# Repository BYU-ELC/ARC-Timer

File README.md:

# ARC-Timer
Autonomous Robotics Competition (BYU) Match Timer

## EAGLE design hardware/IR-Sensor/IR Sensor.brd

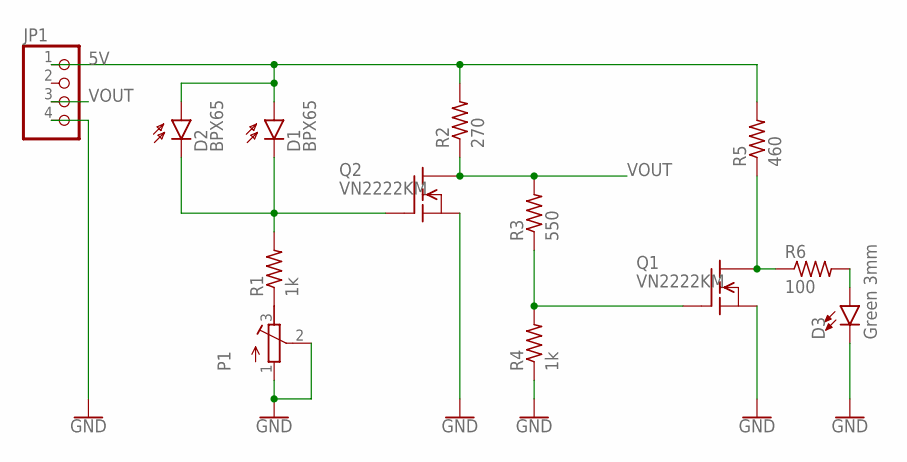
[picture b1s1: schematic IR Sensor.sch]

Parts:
D1, D2: BPX65
D3: Green 3mm; LED_3MM
JP1: PINHD-1X4; 1X04
P1: R-TRIMM64W; RTRIM64W
Q1, Q2: VN2222KM; TO237
R1, R4: 1k; 0204/7
R2: 270; 0204/7
R3: 550; 0204/7
R5: 460; 0204/7
R6: 100; 0204/7

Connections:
5V: D1.A, D2.A, JP1.1, R2.2, R5.2
GND: D3.K (C), JP1.4, P1.1 (A), P1.2 (S), Q1.3 (S), Q2.3 (S), R4.1
unnamed: P1.3 (E), R1.1
unnamed: D1.K (C), D2.K (C), Q2.2 (G), R1.2
unnamed: Q1.2 (G), R3.1, R4.2
unnamed: D3.A, R6.2
unnamed: Q1.1 (D), R5.1, R6.1
VOUT: JP1.3, Q2.1 (D), R2.1, R3.2

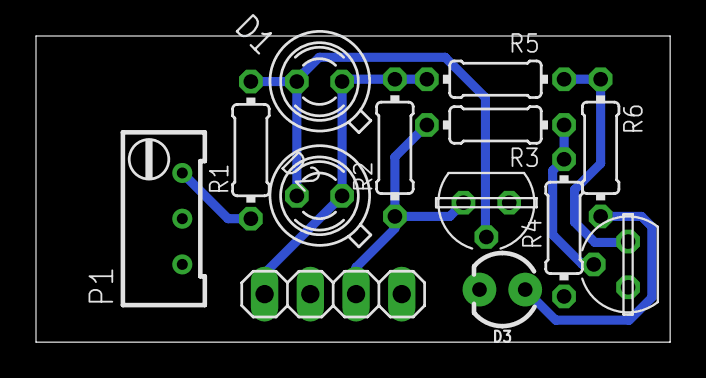
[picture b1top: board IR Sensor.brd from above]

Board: 2 copper layers, 35.2 x 17.0 mm, 13 parts (0 on the bottom side), 8 nets.

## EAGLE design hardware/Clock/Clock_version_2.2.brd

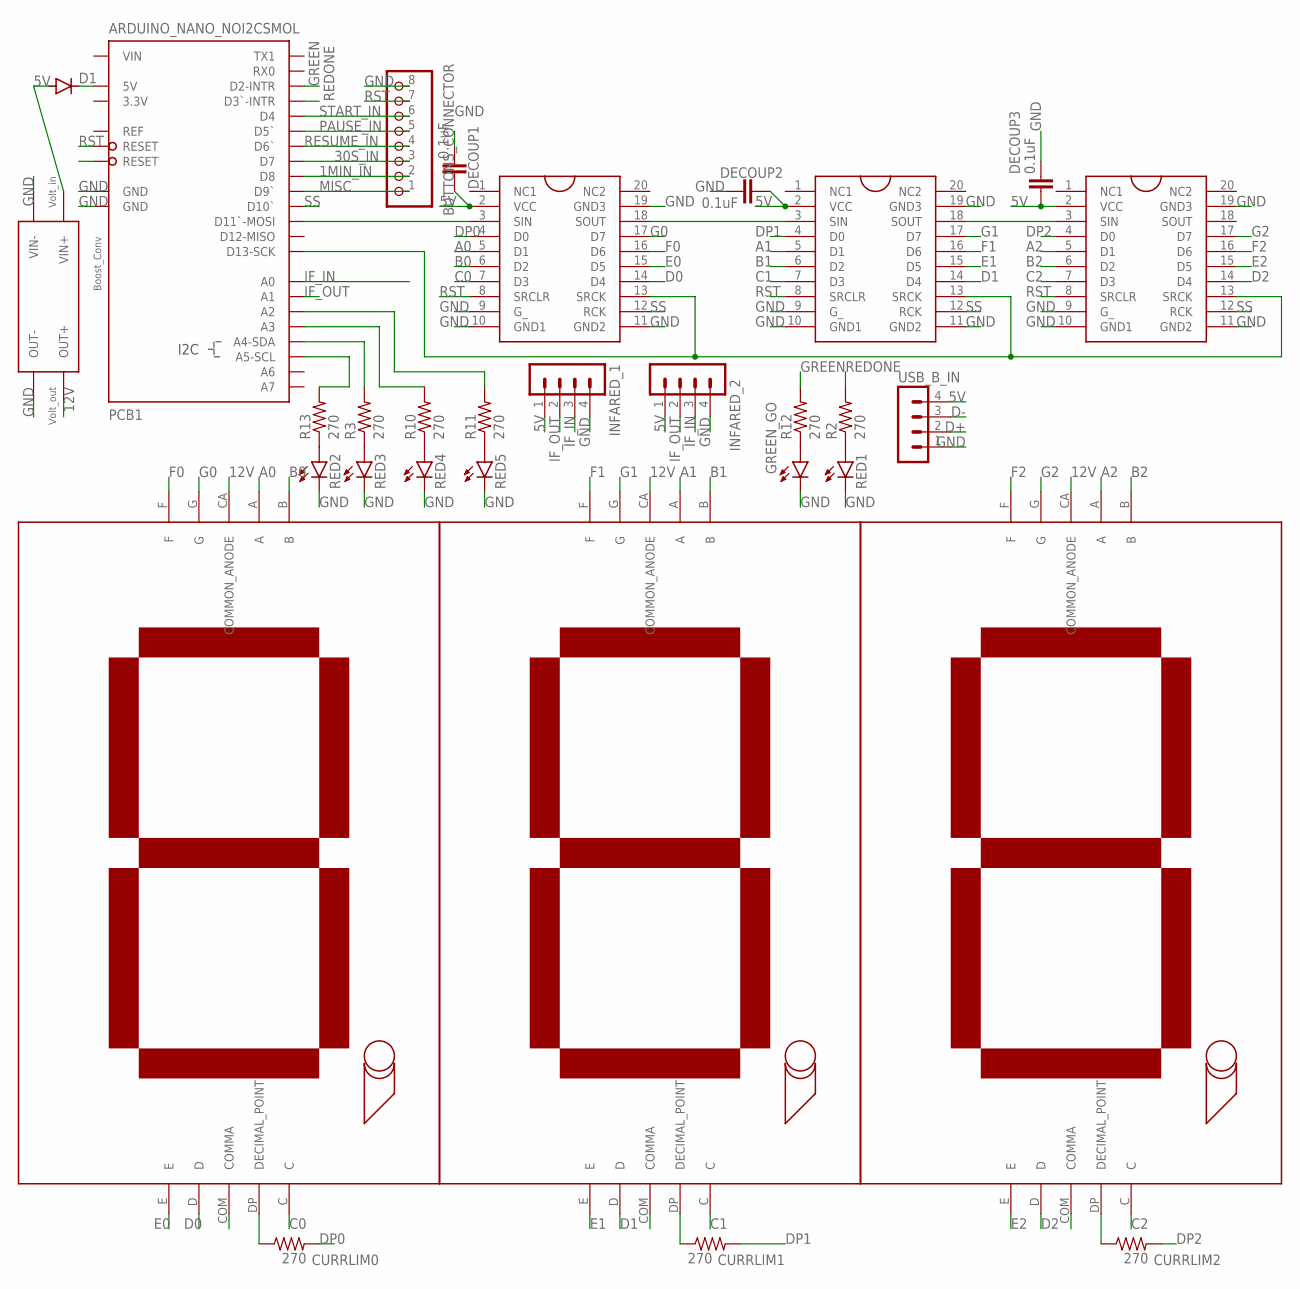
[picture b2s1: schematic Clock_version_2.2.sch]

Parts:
BUTTONS_CONNECTOR: PINHD-1X8/90; 1X08/90
CURRLIM0, CURRLIM1, CURRLIM2: 270; 0207/10
D1: 1N4148DO35-7; DO35-7
DECOUP1, DECOUP2, DECOUP3: 0.1uF; C2.5-2
GREEN_GO: LED5MM
INFARED_1, INFARED_2: MA04-1
MINUTES: 7SEG_LED_A-3001SR; 7SEG_LED
PCB1: ARDUINO_NANO_NOI2CSMOL; ARDUINO_NANO_SMOL
R2, R3, R10, R11, R12, R13: 270; 0207/10
RED1, RED2, RED3, RED4, RED5: LED5MM
SECONDS_ONES: 7SEG_LED_A-3001SR; 7SEG_LED
SECONDS_TENS: 7SEG_LED_A-3001SR; 7SEG_LED
SP0, SP1, SP2: SHIFT_REGISTER_TPIC6C595; SHIFT_REGISTER
U$4: BOOST_CONV
USB_B_IN: MA04-1

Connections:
1MIN_IN: BUTTONS_CONNECTOR.2, PCB1.D8
5V: D1.A, DECOUP1.2, DECOUP2.2, DECOUP3.2, INFARED_1.1, INFARED_2.1, SP0.2 (VCC), SP1.2 (VCC), SP2.2 (VCC), U$4.P$2 (VIN+), USB_B_IN.4
12V: MINUTES.CA (COMMON_ANODE), SECONDS_ONES.CA (COMMON_ANODE), SECONDS_TENS.CA (COMMON_ANODE), U$4.P$3 (OUT+)
30S_IN: BUTTONS_CONNECTOR.3, PCB1.D7
A0: MINUTES.A, SP0.5 (D1)
A1: SECONDS_TENS.A, SP1.5 (D1)
A2: SECONDS_ONES.A, SP2.5 (D1)
B0: MINUTES.B, SP0.6 (D2)
B1: SECONDS_TENS.B, SP1.6 (D2)
B2: SECONDS_ONES.B, SP2.6 (D2)
C0: MINUTES.C, SP0.7 (D3)
C1: SECONDS_TENS.C, SP1.7 (D3)
C2: SECONDS_ONES.C, SP2.7 (D3)
D0: MINUTES.D, SP0.14 (D4)
D1: SECONDS_TENS.D, SP1.14 (D4)
D2: SECONDS_ONES.D, SP2.14 (D4)
D+: USB_B_IN.2
D-: USB_B_IN.3
DP0: CURRLIM0.2, SP0.4 (D0)
DP1: CURRLIM1.2, SP1.4 (D0)
DP2: CURRLIM2.2, SP2.4 (D0)
E0: MINUTES.E, SP0.15 (D5)
E1: SECONDS_TENS.E, SP1.15 (D5)
E2: SECONDS_ONES.E, SP2.15 (D5)
F0: MINUTES.F, SP0.16 (D6)
F1: SECONDS_TENS.F, SP1.16 (D6)
F2: SECONDS_ONES.F, SP2.16 (D6)
G0: MINUTES.G, SP0.17 (D7)
G1: SECONDS_TENS.G, SP1.17 (D7)
G2: SECONDS_ONES.G, SP2.17 (D7)
GND: BUTTONS_CONNECTOR.8, DECOUP1.1, DECOUP2.1, DECOUP3.1, GREEN_GO.K (C), INFARED_1.4, INFARED_2.4, PCB1.GND, PCB1.GND@2 (GND), RED1.K (C), RED2.K (C), RED3.K (C), RED4.K (C), RED5.K (C), SP0.9 (G_), SP0.10 (GND1), SP0.11 (GND2), SP0.19 (GND3), SP1.9 (G_), SP1.10 (GND1), SP1.11 (GND2), SP1.19 (GND3), SP2.9 (G_), SP2.10 (GND1), SP2.11 (GND2), SP2.19 (GND3), U$4.P$1 (VIN-), U$4.P$4 (OUT-), USB_B_IN.1
GREEN: PCB1.D2 (D2-INTR), R12.2
IF_IN: INFARED_1.3, INFARED_2.3, PCB1.A0
IF_OUT: INFARED_1.2, INFARED_2.2, PCB1.A1
MISC: BUTTONS_CONNECTOR.1, PCB1.D9 (D9`)
unnamed: PCB1.D11 (D11`-MOSI), SP0.3 (SIN)
unnamed: D1.C, PCB1.5V
unnamed: CURRLIM0.1, MINUTES.DP (DECIMAL_POINT)
unnamed: CURRLIM1.1, SECONDS_TENS.DP (DECIMAL_POINT)
unnamed: CURRLIM2.1, SECONDS_ONES.DP (DECIMAL_POINT)
unnamed: SP0.18 (SOUT), SP1.3 (SIN)
unnamed: SP1.18 (SOUT), SP2.3 (SIN)
unnamed: PCB1.D13 (D13-SCK), SP0.13 (SRCK), SP1.13 (SRCK), SP2.13 (SRCK)
unnamed: R2.1, RED1.A
unnamed: R13.1, RED2.A
unnamed: R3.1, RED3.A
unnamed: R10.1, RED4.A
unnamed: R11.1, RED5.A
unnamed: GREEN_GO.A, R12.1
unnamed: PCB1.A5 (A5-SCL), R13.2
unnamed: PCB1.A4 (A4-SDA), R3.2
unnamed: PCB1.A3, R10.2
unnamed: PCB1.A2, R11.2
PAUSE_IN: BUTTONS_CONNECTOR.5, PCB1.D5 (D5`)
REDONE: PCB1.D3 (D3`-INTR), R2.2
RESUME_IN: BUTTONS_CONNECTOR.4, PCB1.D6 (D6`)
RST: BUTTONS_CONNECTOR.7, PCB1.RESET, SP0.8 (SRCLR), SP1.8 (SRCLR), SP2.8 (SRCLR)
SS: PCB1.D10 (D10`), SP0.12 (RCK), SP1.12 (RCK), SP2.12 (RCK)
START_IN: BUTTONS_CONNECTOR.6, PCB1.D4

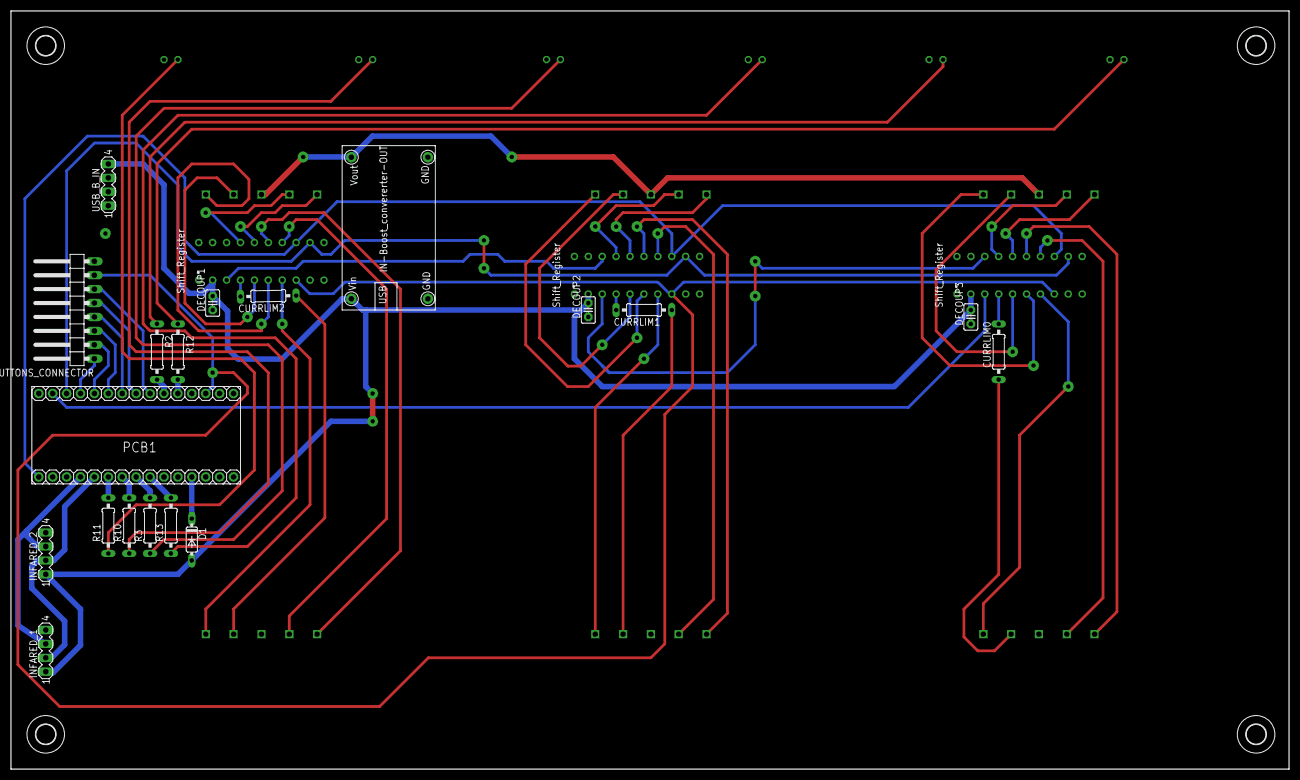
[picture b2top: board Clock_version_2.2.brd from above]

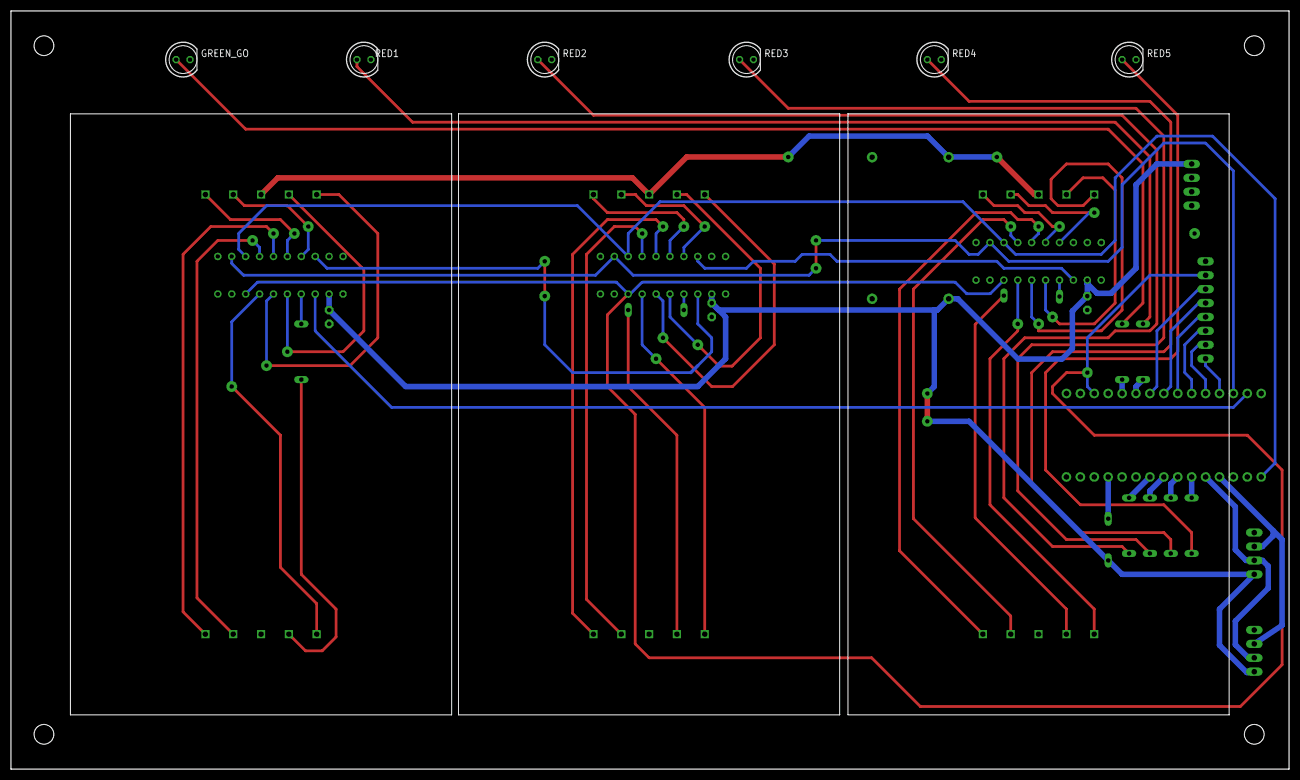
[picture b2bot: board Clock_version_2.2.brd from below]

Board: 2 copper layers, 233.3 x 138.4 mm, 35 parts (9 on the bottom side), 57 nets.

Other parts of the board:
U$1, U$6, U$7, U$8: 3,6

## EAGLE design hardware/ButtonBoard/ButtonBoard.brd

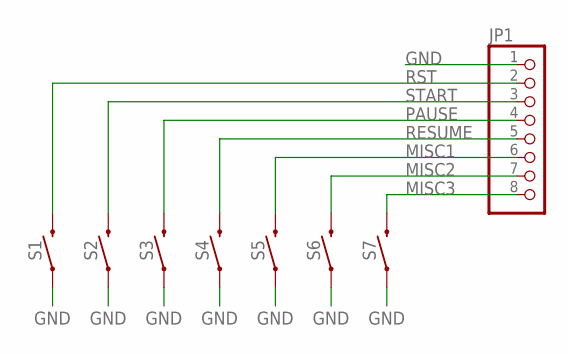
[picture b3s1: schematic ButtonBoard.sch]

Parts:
JP1: PINHD-1X8/90; 1X08/90
S1, S2, S3, S4, S5, S6, S7: MOMENTARY-SWITCH-SPST-SMD-12MM; TACTILE_SWITCH_SMD_12MM

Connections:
GND: JP1.1, S1.1, S2.1, S3.1, S4.1, S5.1, S6.1, S7.1
MISC1: JP1.6, S5.3 (2)
MISC2: JP1.7, S6.3 (2)
MISC3: JP1.8, S7.3 (2)
PAUSE: JP1.4, S3.3 (2)
RESUME: JP1.5, S4.3 (2)
RST: JP1.2, S1.3 (2)
START: JP1.3, S2.3 (2)

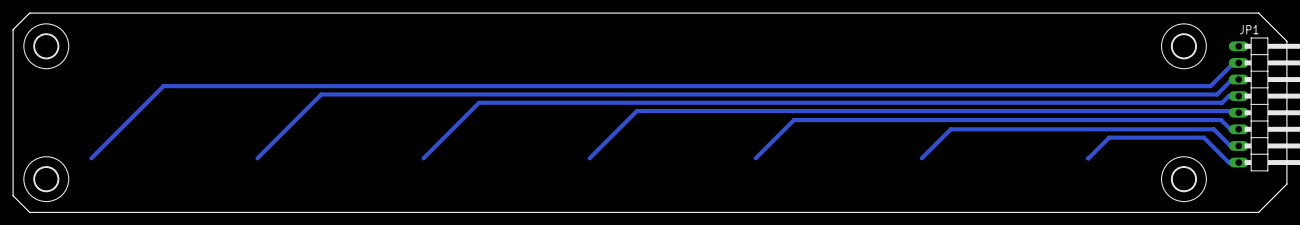
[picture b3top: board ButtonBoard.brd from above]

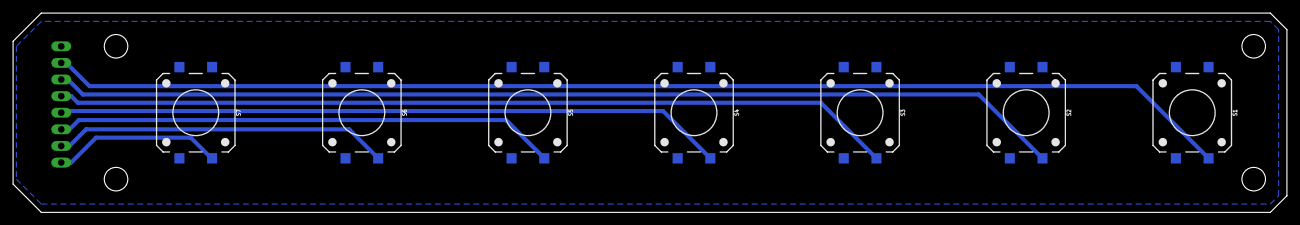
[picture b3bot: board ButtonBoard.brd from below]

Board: 2 copper layers, 194.8 x 30.5 mm, 12 parts (7 on the bottom side), 8 nets.

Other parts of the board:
U$1, U$2, U$3, U$5: 3,6

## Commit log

2023-02-16 Setup Arduino project
2023-02-16 Add timerDisplay module
2023-02-16 include stdint.h in timerDisplay.cpp
2023-02-17 refactor timerDisplay -> display, clarify RCK
2023-02-17 add prototype for timerControl module
2023-02-28 Add buttons file, pin defs, and timer state action
2023-03-03 Update pinDefs, setup basic test program
2023-03-07 Fix initial problems and begin testing
2023-03-14 Fix bug in display driver (working now)
2023-03-14 Add tests used in debugging
2023-03-14 Add buttons module and document
2023-03-14 fix one shot bug
2023-03-16 add leds module
2023-03-16 Add MIT license
2023-03-16 add button test, fix formatting
2023-03-16 change misc button to sub 15 sec button
2023-03-16 add ms time to M.SSS time converter
2023-03-16 add infrared control module
2023-03-16 Write timer control SM
2023-03-16 Setup main file for timer control loop
2023-03-16 fix minor bugs for prototype
2023-03-28 Reorganize project to make space for hw files
2023-03-28 remove local vscode files
2023-03-28 add hardware directory for eagle files
2023-03-28 Add button board
2023-03-28 Rename hardware/ButtonBoard.brd to hardware/ButtonBoard/ButtonBoard.brd
2023-03-28 Rename hardware/ButtonBoard.sch to hardware/ButtonBoard/ButtonBoard.sch
2023-03-28 Rename hardware/eagle.epf to hardware/ButtonBoard/eagle.epf
2023-03-28 Add custom button board library
2023-03-28 add shop cam and drc files
2023-03-28 organize clock files into directory
2023-03-30 Add organization diagram
2023-03-30 add organization image
2023-03-30 Add organization image to README
2023-04-04 increase mounting hole size
2023-04-11 Update pinout and display write order for PCB
2023-04-15 day of debugging
2023-04-16 Change 5sec countdown to start immediately instead of after 1sec
2023-04-16 Add IR sensor hardware eagle files (from Ben D)
2023-04-16 Clean up clock files (remove old revision, misplaced copies)
2023-04-16 moved IR BoM to top level IR hardware dir
2023-04-17 Change infrared input to pullup to prevent float

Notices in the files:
parts and their libraries:
SparkFun-Switches: Licensing: Creative Commons ShareAlike 4.0 International - https://creativecommons.org/licenses/by-sa/4.0
